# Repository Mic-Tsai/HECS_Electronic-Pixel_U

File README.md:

## HECS Electronic | Pixel-U
### Light Painting Equipment

2013 | HECS

We are a visual team of POI arty performers. Design and develop the light-painting equipment which contains picture & dynamic presentation. This was my college side project during 2013-2014 in KUAS (National Kaohsiung University of Applied Sciences, Taiwan).

- [Promotional Video](https://youtu.be/c2NhDoxItCM)

2017 | Pixel-X

  Re-engineering hardware part, split the core as controller and display, purpose to minimum PCB after-assemble space. LEDs used the improved version SK6812B-3535 (package) from WS2812B-5050, got better heat radiating, the smaller dots will increase the image resolution.

**2018 | Pixel-U**

  **Base on Pixel-X prototype used the same controller board, rebuild the display layout up to 40 LEDs which is smaller package (SK6812B-2427). System compare detail please refer the following slide.**

```
Arduino tool kit, and require the following material:
- MCU: ATmega328p
- Storage: SD card
- Display: SK6812B-2427
- Power source: Li-Po Battery
```

##

### **About Mic**

Director of HECS, design light painting product that contains hardware layout and software programming.

- [Resume](https://drive.google.com/file/d/1NEWwNo3X4ogJMNzp6jpFyT0a6GPGhs7Q/view)

## 

### **About HECS**

Interesting how it works please refer for detail:

- [HECS ISSUU](https://issuu.com/56905554/docs/hecs_book)

- [HECS ISSUU moble device](https://issuu.com/56905554/docs/hecs-book_issuu)

- [HECS Electronics](https://drive.google.com/file/d/1tgr780FQ_Ib0JO3FdQn_M6LVbDeVmUmG/view?usp=sharing)

## 

### **About Hardware**

If you want to buy this board and are in Taiwan, please visit my shop: 

Will OPEN SOON:
* [HECS SHOP](https://www.)
* Contact me via mail (xbcke12345@gmail.com)
* If this project helping. Please generously support =)

## 

## 

>### License Information
>>This product is open source! Both, our hardware and software are open source and licensed under the following:
>>#### Hardware
>>>All hardware is released under [Creative Commons Share-alike 4.0 International](http://creativecommons.org/licenses/by-sa/4.0/)
>>#### Software 
>>>All software is released under the MIT License [http://opensource.org/licenses/MIT](http://opensource.org/licenses/MIT)
>>#### Documentation
>>>The documentation on this page is released under [Creative Commons Share-alike 4.0 International](http://creativecommons.org/licenses/by-sa/4.0/)

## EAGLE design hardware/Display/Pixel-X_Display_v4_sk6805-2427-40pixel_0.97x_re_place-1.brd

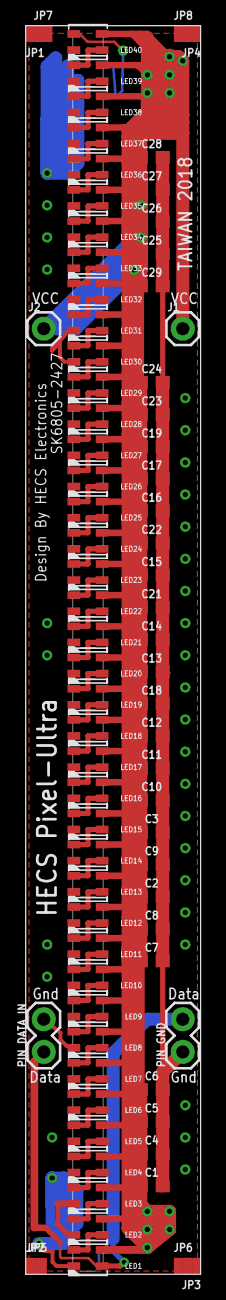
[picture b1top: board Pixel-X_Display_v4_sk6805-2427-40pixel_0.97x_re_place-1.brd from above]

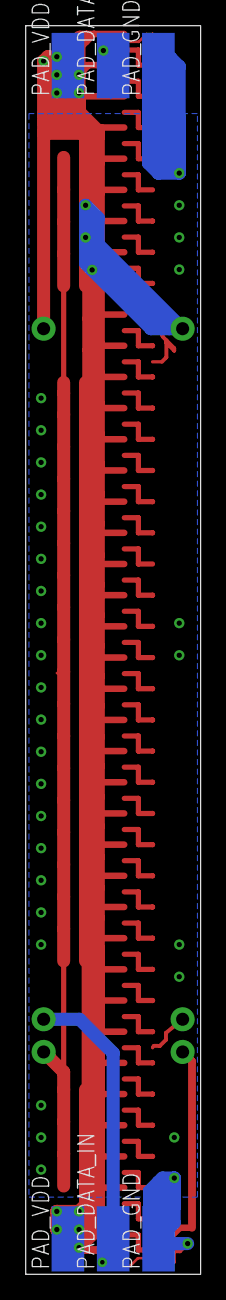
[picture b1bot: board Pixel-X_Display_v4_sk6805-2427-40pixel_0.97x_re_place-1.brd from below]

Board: 2 copper layers, 13.6 x 97.1 mm, 86 parts (6 on the bottom side), 43 nets.

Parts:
C1, C2, C3, C4, C5, C6, C7, C8, C9, C10, C11, C12, C13, C14, C15, C16, C17, C18, C19, C21, C22, C23, C24, C25, C26, C27, C28, C29: 0.1uF; 0603
J1, J2: 1X01
JP1, JP2, JP3, JP4, JP5, JP6, JP7, JP8: JUMPER-SMT_2_NO_NO-SILK; SMT-JUMPER_2_NO_NO-SILK
LED1, LED2, LED3, LED4, LED5, LED6, LED7, LED8, LED9, LED10, LED11, LED12, LED13, LED14, LED15, LED16, LED17, LED18, LED19, LED20, LED21, LED22, LED23, LED24, LED25, LED26, LED27, LED28, LED29, LED30, LED31, LED32, LED33, LED34, LED35, LED36, LED37, LED38, LED39, LED40: WS2812BSK68052427; LED3535
PAD_DATA_IN: SMD2,54-5,08
PAD_DATA_OUT: SMD2,54-5,08
PAD_GND, PAD_GND1: SMD2,54-5,08
PAD_VDD, PAD_VDD1: SMD2,54-5,08
PIN_DATA_IN: 1X02
PIN_GND: 1X02

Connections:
+5V: C1.1, C2.1, C3.1, C4.1, C5.1, C6.1, C7.1, C8.1, C9.1, C10.1, C11.1, C12.1, C13.1, C14.1, C15.1, C16.1, C17.1, C18.1, C19.1, C21.1, C22.1, C23.1, C24.1, C25.1, C26.1, C27.1, C28.1, C29.1, J1.1, J2.1, LED1.2, LED2.2, LED3.2, LED4.2, LED5.2, LED6.2, LED7.2, LED8.2, LED9.2, LED10.2, LED11.2, LED12.2, LED13.2, LED14.2, LED15.2, LED16.2, LED17.2, LED18.2, LED19.2, LED20.2, LED21.2, LED22.2, LED23.2, LED24.2, LED25.2, LED26.2, LED27.2, LED28.2, LED29.2, LED30.2, LED31.2, LED32.2, LED33.2, LED34.2, LED35.2, LED36.2, LED37.2, LED38.2, LED39.2, LED40.2, PAD_VDD.1, PAD_VDD1.1
COM: C1.2, C2.2, C3.2, C4.2, C5.2, C6.2, C7.2, C8.2, C9.2, C10.2, C11.2, C12.2, C13.2, C14.2, C15.2, C16.2, C17.2, C18.2, C19.2, C21.2, C22.2, C23.2, C24.2, C25.2, C26.2, C27.2, C28.2, C29.2, LED1.4, LED2.4, LED3.4, LED4.4, LED5.4, LED6.4, LED7.4, LED8.4, LED9.4, LED10.4, LED11.4, LED12.4, LED13.4, LED14.4, LED15.4, LED16.4, LED17.4, LED18.4, LED19.4, LED20.4, LED21.4, LED22.4, LED23.4, LED24.4, LED25.4, LED26.4, LED27.4, LED28.4, LED29.4, LED30.4, LED31.4, LED32.4, LED33.4, LED34.4, LED35.4, LED36.4, LED37.4, LED38.4, LED39.4, LED40.4, PAD_GND.1, PAD_GND1.1, PIN_DATA_IN.2, PIN_GND.1
unnamed: LED1.1, PAD_DATA_IN.1, PIN_DATA_IN.1, PIN_GND.2
unnamed: LED1.3, LED2.1
unnamed: LED2.3, LED3.1
unnamed: LED3.3, LED4.1
unnamed: LED4.3, LED5.1
unnamed: LED5.3, LED6.1
unnamed: LED29.3, LED30.1
unnamed: LED6.3, LED7.1
unnamed: LED7.3, LED8.1
unnamed: LED8.3, LED9.1
unnamed: LED9.3, LED10.1
unnamed: LED10.3, LED11.1
unnamed: LED11.3, LED12.1
unnamed: LED12.3, LED13.1
unnamed: LED13.3, LED14.1
unnamed: LED15.3, LED16.1
unnamed: LED16.3, LED17.1
unnamed: LED17.3, LED18.1
unnamed: LED18.3, LED19.1
unnamed: LED19.3, LED20.1
unnamed: LED14.3, LED15.1
unnamed: LED20.3, LED21.1
unnamed: LED21.3, LED22.1
unnamed: LED22.3, LED23.1
unnamed: LED23.3, LED24.1
unnamed: LED24.3, LED25.1
unnamed: LED25.3, LED26.1
unnamed: LED26.3, LED27.1
unnamed: LED27.3, LED28.1
unnamed: LED28.3, LED29.1
unnamed: LED30.3, LED31.1
unnamed: LED39.3, LED40.1
unnamed: LED38.3, LED39.1
unnamed: LED37.3, LED38.1
unnamed: LED36.3, LED37.1
unnamed: LED35.3, LED36.1
unnamed: LED34.3, LED35.1
unnamed: LED33.3, LED34.1
unnamed: LED32.3, LED33.1
unnamed: LED31.3, LED32.1
unnamed: LED40.3, PAD_DATA_OUT.1

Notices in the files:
parts and their libraries:
SparkFun-Capacitors: Licensing: Creative Commons ShareAlike 4.0 International - https://creativecommons.org/licenses/by-sa/4.0
